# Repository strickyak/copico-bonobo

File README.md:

# copico-bonobo
KICAD: Simple and cheap PI PICO cartridge for Coco; can spoonfeed to boot, and has Control &amp; Data ports decoded.

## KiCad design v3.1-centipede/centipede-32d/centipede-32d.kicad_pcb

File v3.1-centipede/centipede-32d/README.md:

# Centipede 32d

TO DO -- document better.

This is pretty much a RP2350B microcontroller with direct connections
to the Radio Shack Color Computer's 40-pin expansion bus.

The RP2350B may be powered either by the USB-C or by the Coco.
The USB-C takes precedence by going through only one diode
to VBUS, whereas the Coco's +5V input goes through two diodes.

Jumper J6 must be configured in one of two ways:

*   Preferred: Connect pins 2 and 3, and connect pins 4 and 5.
    This runs both E and Q through the schmidt trigger inverter
    to clean them.   They arrive negated at GPIO 21 and 22.

*   Original:  Connect pins 1 and 2, and pins 5 and 6.
    This runs E and Q direct to GPIO 21 and 22, not negated.
    This has problems with bouncy detection.

## Maybe a BUG? VBUS powers the 74HC14.

## Bug: CTS

On a coco3, we must obey CTS, not just the address range $C000-$DFFF.

Temporarily I'm bodging it from J5 to J4, CTS (negative logic) to GPIO18.

## Clock Speed

My current PIO-less firmware works with the semi-fast poke ($FFD7)
but not with the fast poke ($FFD9).   That's with disk11.asm for
Disk Basic Cart ROM, and a floppy at $FF40/$FF4[89AB].

Testing on a 16K Coco2 (named "2C") and a Coco3 with a 6309
and 512K RAM (named "3B").

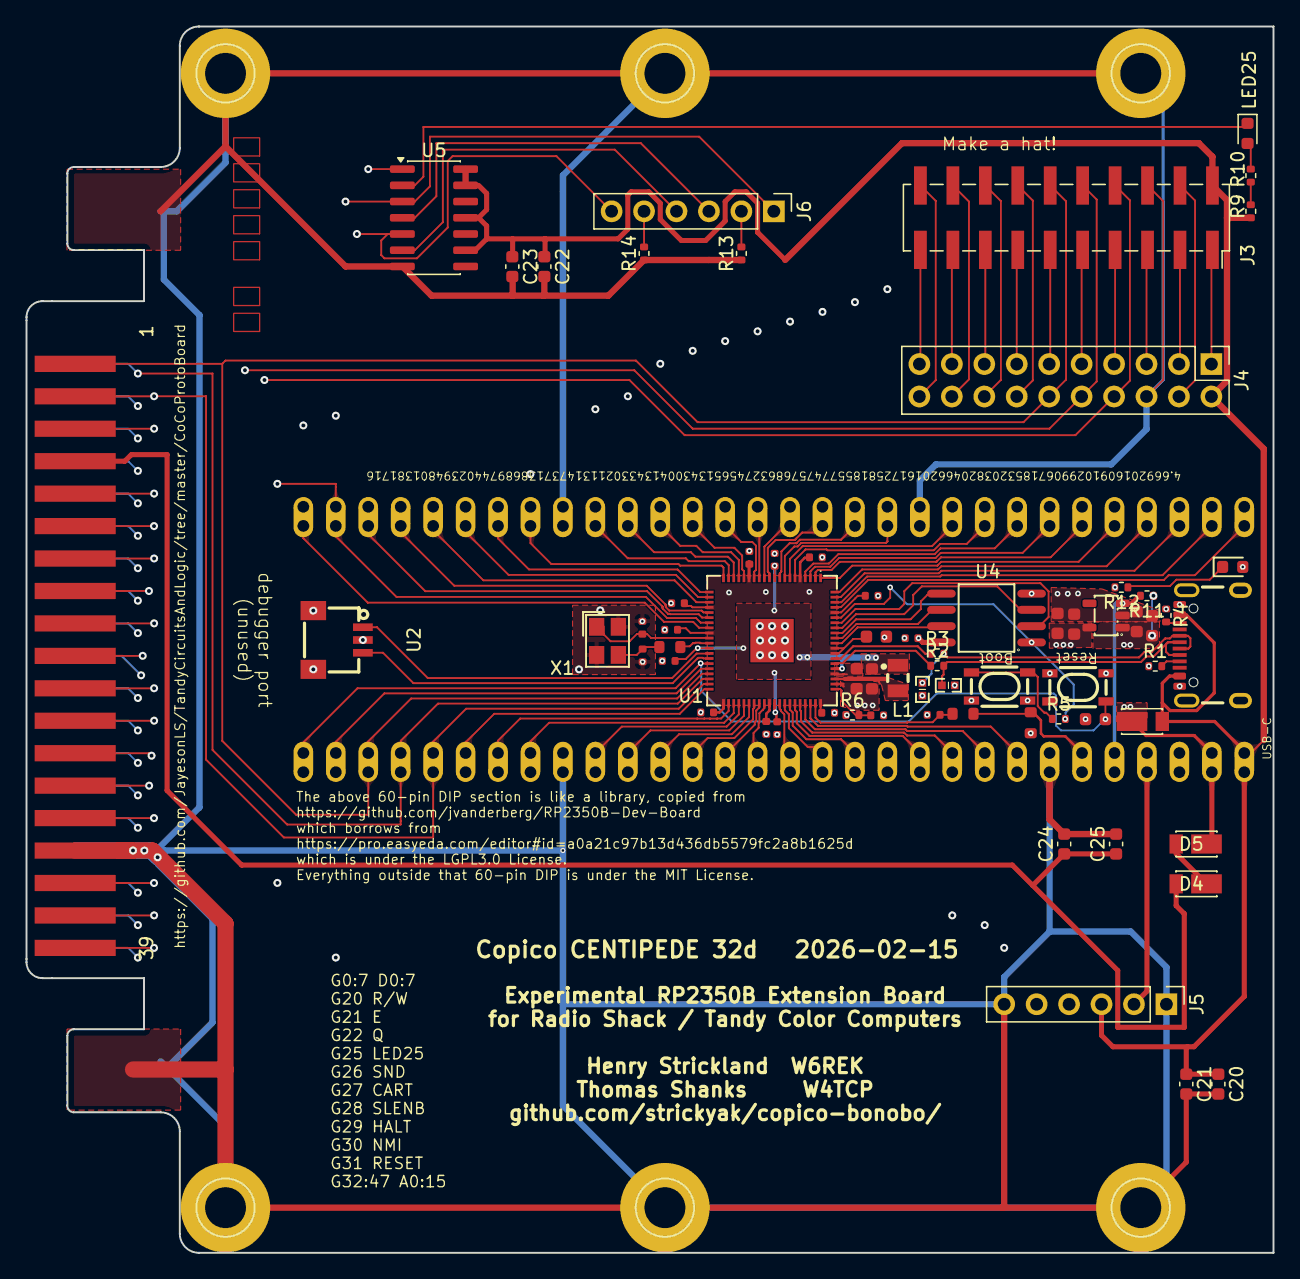
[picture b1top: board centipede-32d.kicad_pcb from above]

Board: 4 copper layers, 97.6 x 96.0 mm, 127 parts (0 on the bottom side), 89 nets.

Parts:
3V3_EN1, 3V31: Castellated Pad
ADC_VREF1: Castellated Pad
Boot1: K2-1808SN-A4SW-01; KEY-SMD_4P-L4.2-W3.2-P2.20-LS5.1-TL
C1, C2, C3, C4, C5, C6, C7, C8, C13, C14, C16, C36: 100nF; C_0402
C9, C15, C38, C39: 100nF; C_0603
C10, C12: 4.7uF; C_0603
C11, C19: 4.7uF; C_0402
C17, C18: 15pF; C_0402
C20, C22, C24: 10uF; C_0603_1608Metric
C21, C23, C25: 100nF; C_0603_1608Metric
C37, C40: 10uF; C_0603
D1, D4, D5: POWERDI-123_L2.8-W1.8-LS3.7-RD
D2, D3: RCLAMP0521P.TCT-MS; D0402-BI
GND1, GND2, GND3, GND4, GND4#2, GND6: Castellated Pad
GPI10: Castellated Pad
GPIO0, GPIO1, GPIO1#2, GPIO1#3, GPIO1#4, GPIO1#5, GPIO1#6, GPIO1#7, GPIO1#8, GPIO2, GPIO3, GPIO4, GPIO5, GPIO7, GPIO8, GPIO11, GPIO12, GPIO13, GPIO15, GPIO16, GPIO17, GPIO18, GPIO19, GPIO21, GPIO21#2, GPIO22, GPIO24, GPIO25, GPIO26, GPIO27, GPIO28, GPIO29, GPIO30, GPIO32, GPIO34, GPIO35, GPIO36, GPIO37, GPIO38, GPIO39, GPIO40, GPIO41, GPIO42, GPIO43, GPIO44, GPIO45, GPIO46: Castellated Pad
J3: Conn_02x10_Odd_Even; PinSocket_2x10_P2.54mm_Vertical_SMD
J4: Conn_02x10_Odd_Even; PinHeader_2x10_P2.54mm_Vertical
J5, J6: Conn_01x06; PinHeader_1x06_P2.54mm_Vertical
L1: IND-SMD_L2.0-W1.6_AOTA-B201610S3R3-101-T
LED25: Red; LED_0603_1608Metric
P1: CocoEdgeConnector; CocoCardEdgeCocoMIDI
PWR_LED1: Red; D_0603
R1, R4: 5.1kΩ; R_0402_1005Metric
R2, R3, R6: 33Ω; R_0402_1005Metric
R5: 1kΩ; R_0402_1005Metric
R7: 1Ω; R_0603
R8: 200Ω; R_0603
R9, R10, R12: 2kΩ; R_0402_1005Metric
R11: 100kΩ; R_0402_1005Metric
R13, R14: 10kΩ; R_0402_1005Metric
R28: 1kΩ; R_0603
RUN1: Castellated Pad
Reset1: K2-1808SN-A4SW-01; KEY-SMD_4P-L4.2-W3.2-P2.20-LS5.1-TL
U1: QFN-80_L10.0-W10.0-P0.40-TL-EP3.4
U2: HC-1.0-3PWT; CONN-SMD_SM03B-SRSS-TB-LF-SN-P
U3: SOT-23-5_L3.0-W1.7-P0.95-LS2.8-BR
U4: W25Q128; SOIC-8_L5.3-W5.3-P1.27-LS8.0-BL
U5: 74HC14; SOIC-14_3.9x8.7mm_P1.27mm
USB1: USB-C-SMD_TYPE-C-6PIN-2MD-073
VBUS1: Castellated Pad
VSYS1: Castellated Pad
X1: CRYSTAL-SMD_4P-L3.2-W2.5-BL

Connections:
1V1: C2.1, C5.1, C10.2, C13.2, L1.2, U1.10 (DVDD), U1.32 (DVDD), U1.51 (DVDD), U1.65 (VREG_FB)
3V3: 3V31.57, C1.1, C3.1, C4.1, C6.1, C7.1, C8.2, C9.2, C12.2, C14.2, C16.2, C36.2, C38.1, C40.1, J3.4, J4.4, J5.2, PWR_LED1.2, R6.1, R8.2, U1.5 (IOVDD), U1.15 (IOVDD), U1.24 (IOVDD), U1.29 (IOVDD), U1.41 (IOVDD), U1.50 (IOVDD), U1.60 (IOVDD), U1.64 (VREG_VIN), U1.68 (USB_OTP_VDD), U1.69 (QSPI_IOVDD), U1.76 (IOVDD), U3.5 (VOUT), U4.8 (VCC)
3V3_EN: 3V3_EN1.56, R11.2, U3.3 (CE)
/VREG_LX: L1.1, U1.63 (VREG_LX)
ADC_VREF: ADC_VREF1.55, R7.2, R8.1
Coco5V: C24.1, C25.1, D4.2, P1.9 (+5V)
Eclock: J6.1, P1.6 (E), U5.3
GND: Boot1.3, Boot1.4, C1.2, C2.2, C3.2, C4.2, C5.2, C6.2, C7.2, C8.1, C9.1, C10.1, C11.1, C12.1, C13.1, C14.1, C15.1, C16.1, C17.2, C18.1, C19.2, C20.2, C21.2, C22.2, C23.2, C24.2, C25.2, C36.1, C37.2, C38.2, C39.2, C40.2, D2.1, D3.1, GND2.22, GND3.39, GND4.49, GND4#2.54, GND6.58, GPI10.11, J3.6, J4.6, J5.1, J5.6, P1.33 (GND), P1.34 (GND), R1.1, R4.1, R12.2, R13.1, R14.1, Reset1.3, Reset1.4, U1.62 (VREG_PGND), U1.81 (GND), U2.2, U2.4, U2.5, U3.2 (VSS), U4.4 (GND), U5.7 (GND), USB1.1 (GND), USB1.12 (GND), USB1.13 (SHELL), USB1.14 (SHELL), X1.2 (GND), X1.4 (GND)
GPIO0: GPIO0.1, P1.10 (D0), U1.77 (GPIO0)
GPIO1: GPIO1#2.2, P1.11 (D1), U1.78 (GPIO1)
GPIO2: GPIO2.3, P1.12 (D2), U1.79 (GPIO2)
GPIO3: GPIO3.4, P1.13 (D3), U1.80 (GPIO3)
GPIO4: GPIO4.5, P1.14 (D4), U1.1 (GPIO4)
GPIO5: GPIO5.6, P1.15 (D5), U1.2 (GPIO5)
GPIO6: GPIO1#8.7, P1.16 (D6), U1.3 (GPIO6)
GPIO7: GPIO7.8, P1.17 (D7), U1.4 (GPIO7)
GPIO8: GPIO8.9, J3.1, J4.1, U1.6 (GPIO8)
GPIO9: GPIO1#7.10, J3.3, J4.3, U1.7 (GPIO9)
GPIO10: GND1.12, J3.5, J4.5, U1.8 (GPIO10)
GPIO11: GPIO11.13, J3.7, J4.7, U1.9 (GPIO11)
GPIO12: GPIO12.14, J3.9, J4.9, U1.11 (GPIO12)
GPIO13: GPIO13.15, J3.11, J4.11, U1.12 (GPIO13)
GPIO14: GPIO1#6.16, J3.13, J4.13, U1.13 (GPIO14)
GPIO15: GPIO15.17, J3.15, J4.15, U1.14 (GPIO15)
GPIO16: GPIO16.18, J3.17, J4.17, U1.16 (GPIO16)
GPIO17: GPIO17.19, J3.19, J4.19, U1.17 (GPIO17)
GPIO18: GPIO18.20, J3.20, J4.20, U1.18 (GPIO18)
GPIO19: GPIO19.21, J3.18, J4.18, U1.19 (GPIO19)
GPIO20: GPIO21.23, P1.18 (R/~W), U1.20 (GPIO20)
GPIO21: GPIO21#2.24, J6.2, R13.2, U1.21 (GPIO21)
GPIO22: GPIO22.25, J6.5, R14.2, U1.22 (GPIO22)
GPIO23: GPIO1#5.26, U1.23 (GPIO23)
GPIO24: GPIO24.27, U1.25 (GPIO24)
GPIO25: GPIO25.28, U1.26 (GPIO25), U5.1
GPIO26: GPIO26.29, J3.16, J4.16, P1.35 (SND), U1.27 (GPIO26)
GPIO27: GPIO27.30, J3.14, J4.14, P1.8 (~CART), U1.28 (GPIO27)
GPIO28: GPIO28.31, P1.40 (~SLENB), U1.36 (GPIO28)
GPIO29: GPIO29.33, J3.12, J4.12, P1.3 (~HALT), U1.37 (GPIO29)
GPIO30: GPIO30.34, J3.10, J4.10, P1.4 (~NMI), U1.38 (GPIO30)
GPIO31: GPIO1#4.1, GPIO1#4.35, J3.8, J4.8, P1.5 (~RESET), U1.39 (GPIO31)
GPIO32: GPIO1.36, P1.19 (A0), U1.40 (GPIO32)
GPIO33: GPIO32.37, P1.20 (A1), U1.42 (GPIO33)
GPIO34: GPIO34.38, P1.21 (A2), U1.43 (GPIO34)
GPIO35: GPIO35.40, P1.22 (A3), U1.44 (GPIO35)
GPIO36: GPIO36.41, P1.23 (A4), U1.45 (GPIO36)
GPIO37: GPIO37.42, P1.24 (A5), U1.46 (GPIO37)
GPIO38: GPIO38.43, P1.25 (A6), U1.47 (GPIO38)
GPIO39: GPIO39.44, P1.26 (A7), U1.48 (GPIO39)
GPIO40/ADC0: GPIO40.45, P1.27 (A8), U1.49 (GPIO40_ADC0)
GPIO41/ADC1: GPIO41.46, P1.28 (A9), U1.52 (GPIO41_ADC1)
GPIO42/ADC2: GPIO42.47, P1.29 (A10), U1.53 (GPIO42_ADC2)
GPIO43/ADC3: GPIO43.48, P1.30 (A11), U1.54 (GPIO43_ADC3)
GPIO44/ADC4: GPIO44.50, P1.31 (A12), U1.55 (GPIO44_ADC4)
GPIO45/ADC5: GPIO45.51, P1.37 (A13), U1.56 (GPIO45_ADC5)
GPIO46/ADC6: GPIO46.52, P1.38 (A14), U1.57 (GPIO46_ADC6)
GPIO47/ADC7: GPIO1#3.53, P1.39 (A15), U1.58 (GPIO47_ADC7)
LED25a: LED25.1, U5.2
LED25b: LED25.2, R10.1
unnamed: Boot1.1, Boot1.2, R5.1
unnamed: C17.1, R28.1, X1.3
unnamed: D4.1, D5.2
unnamed: PWR_LED1.1, R12.1
unnamed: R9.1, R10.2
unnamed: C19.1, R7.1, U1.59 (ADC_AVDD)
unnamed: U1.71 (QSPI_SCLK), U4.6 (CLK)
unnamed: U1.72 (QSPI_SD0), U4.5 (DI)
unnamed: U1.74 (QSPI_SD1), U4.2 (DO)
unnamed: U1.73 (QSPI_SD2), U4.3 (IO2)
unnamed: U1.70 (QSPI_SD3), U4.7 (IO3)
unnamed: R5.2, U1.75 (QSPI_SS), U4.1 (CS#)
unnamed: U1.33 (SWCLK), U2.1
unnamed: U1.34 (SWDIO), U2.3
unnamed: R2.1, U1.66 (USB_DM)
unnamed: R3.1, U1.67 (USB_DP)
unnamed: C11.2, R6.2, U1.61 (VREG_AVDD)
unnamed: C18.2, U1.30 (XIN), X1.1
unnamed: R28.2, U1.31 (XOUT)
unnamed: R1.2, USB1.4 (CC1)
unnamed: R4.2, USB1.10 (CC2)
Qclock: J6.6, P1.7 (Q), U5.5
RUN: C15.2, RUN1.30, Reset1.1, U1.35 (RUN)
USB2_D+: D3.2, R3.2, USB1.6 (DP1), USB1.8 (DP2)
USB2_D-: D2.2, R2.2, USB1.5 (DN2), USB1.7 (DN1)
VBUS: C20.1, C21.1, C22.1, C23.1, D1.2, J3.2, J4.2, J5.3, R9.2, U5.9, U5.11, U5.13, U5.14 (VCC), USB1.2 (VBUS), USB1.11 (VBUS), VBUS1.60
VSYS: C37.1, C39.1, D1.1, D5.1, R11.1, U3.1 (VIN), VSYS1.59
nCTS: J5.4, P1.32 (~CTS)
nEclock: J6.3, U5.4
nQclock: J6.4, U5.6
nSCS: J5.5, P1.36 (~SCS)

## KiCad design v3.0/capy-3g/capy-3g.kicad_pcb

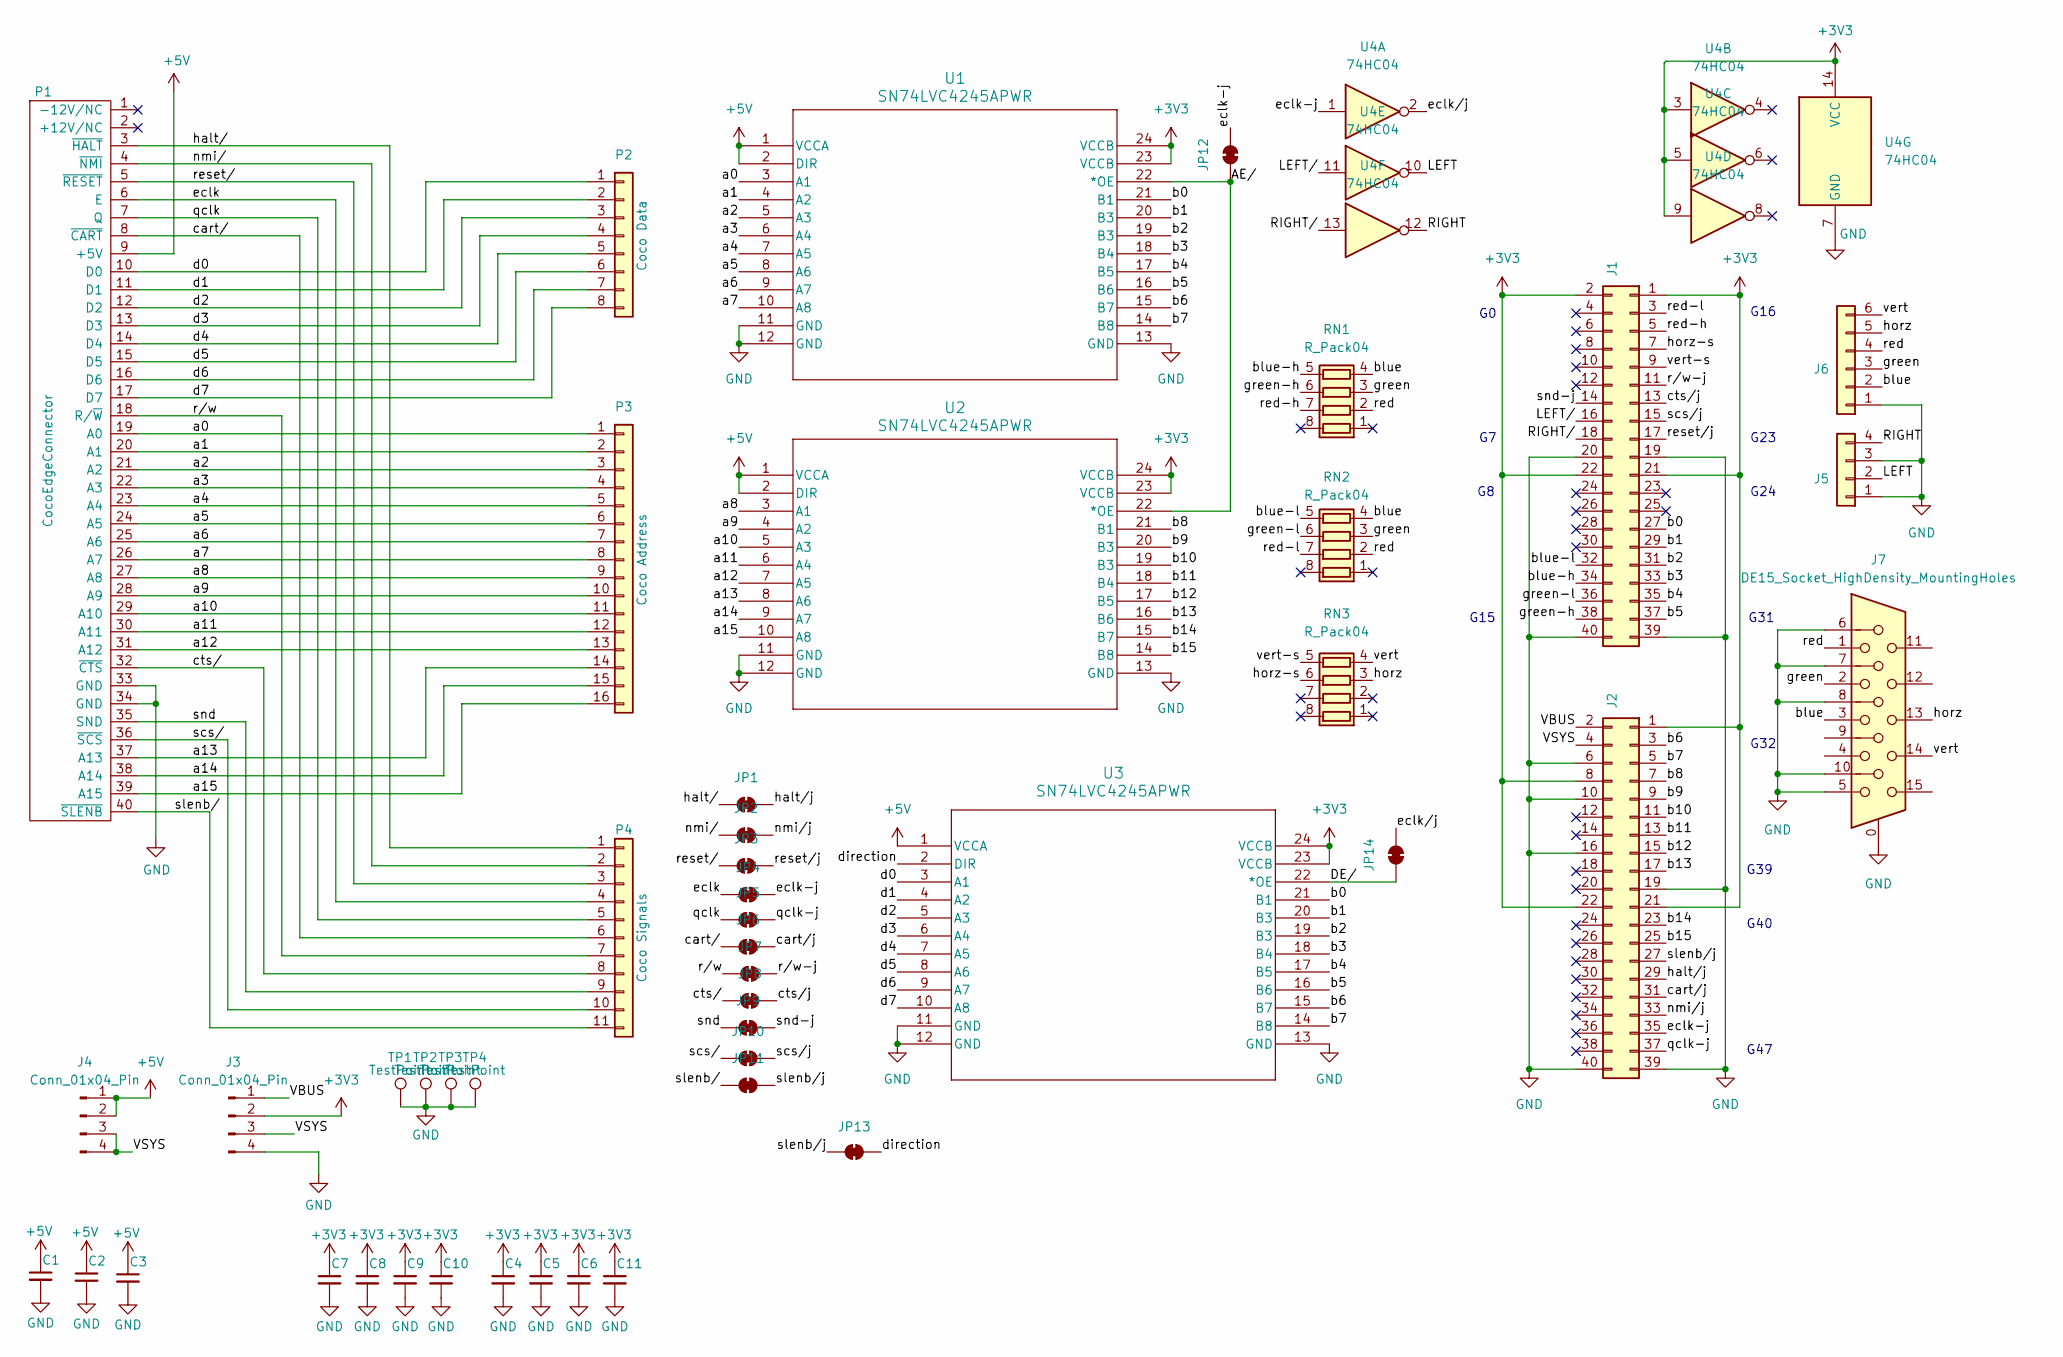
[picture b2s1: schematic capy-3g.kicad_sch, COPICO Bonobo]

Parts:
C1, C2, C3, C4, C5, C6, C7, C8, C9, C10, C11: C_Small; C_0402_1005Metric
J1, J2: Conn_02x20_Odd_Even; PinHeader_2x20_P2.54mm_Vertical
J3, J4: Conn_01x04_Pin; PinHeader_1x04_P2.54mm_Vertical
J5: Conn_01x04; PinHeader_1x04_P2.54mm_Vertical
J6: Conn_01x06; PinHeader_1x06_P2.54mm_Vertical
J7: DE15_Socket_HighDensity_MountingHoles; DSUB-15-HD_Socket_Vertical_P2.29x1.98mm_MountingHoles
JP1, JP2, JP3, JP4, JP5, JP6, JP7, JP8, JP9, JP10, JP11, JP12, JP13, JP14: SolderJumper_2_Bridged; SolderJumper-2_P1.3mm_Bridged_RoundedPad1.0x1.5mm
P1: CocoEdgeConnector; CocoCardEdgeCocoMIDI
P2: Coco Data; DIP-16_W7.62mm
P3: Coco Address; DIP-32_W15.24mm
P4: Coco Signals; DIP-22_W10.16mm
RN1, RN2, RN3: R_Pack04; R_Array_Convex_4x0603
TP1, TP2, TP3, TP4: TestPoint; TestPoint_Plated_Hole_D4.0mm
U1, U2, U3: SN74LVC4245APWR; TSSOP-24_4.4x7.8mm_P0.65mm
U4: 74HC04; TSSOP-14_4.4x5mm_P0.65mm

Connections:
+3V3: C4.1, C5.1, C6.1, C7.1, C8.1, C9.1, C10.1, C11.1, J1.1, J1.2, J1.21, J1.22, J2.1, J2.8, J2.21, J2.22, J3.2, U1.23 (VCCB), U1.24 (VCCB), U2.23 (VCCB), U2.24 (VCCB), U3.23 (VCCB), U3.24 (VCCB), U4.3, U4.5, U4.9, U4.14 (VCC)
+5V: C1.1, C2.1, C3.1, J4.1, J4.2, P1.9 (+5V), U1.1 (VCCA), U1.2 (DIR), U2.1 (VCCA), U2.2 (DIR), U3.1 (VCCA)
/AE/: JP12.1 (A), U1.22 (*OE), U2.22 (*OE)
/DE/: JP14.1 (A), U3.22 (*OE)
/LEFT: J5.2, U4.10
/LEFT/: J1.16, U4.11
/RIGHT: J5.4, U4.12
/RIGHT/: J1.18, U4.13
/VBUS: J2.2, J3.1
/VSYS: J2.4, J3.3, J4.3, J4.4
/a0: P1.19 (A0), P3.1, U1.3 (A1)
/a1: P1.20 (A1), P3.2, U1.4 (A2)
/a2: P1.21 (A2), P3.3, U1.5 (A3)
/a3: P1.22 (A3), P3.4, U1.6 (A4)
/a4: P1.23 (A4), P3.5, U1.7 (A5)
/a5: P1.24 (A5), P3.6, U1.8 (A6)
/a6: P1.25 (A6), P3.7, U1.9 (A7)
/a7: P1.26 (A7), P3.8, U1.10 (A8)
/a8: P1.27 (A8), P3.9, U2.3 (A1)
/a9: P1.28 (A9), P3.10, U2.4 (A2)
/a10: P1.29 (A10), P3.11, U2.5 (A3)
/a11: P1.30 (A11), P3.12, U2.6 (A4)
/a12: P1.31 (A12), P3.13, U2.7 (A5)
/a13: P1.37 (A13), P3.14, U2.8 (A6)
/a14: P1.38 (A14), P3.15, U2.9 (A7)
/a15: P1.39 (A15), P3.16, U2.10 (A8)
/b0: J1.27, U1.21 (B1), U3.21 (B1)
/b1: J1.29, U1.20 (B3), U3.20 (B3)
/b2: J1.31, U1.19 (B3), U3.19 (B3)
/b3: J1.33, U1.18 (B4), U3.18 (B4)
/b4: J1.35, U1.17 (B5), U3.17 (B5)
/b5: J1.37, U1.16 (B6), U3.16 (B6)
/b6: J2.3, U1.15 (B7), U3.15 (B7)
/b7: J2.5, U1.14 (B8), U3.14 (B8)
/b8: J2.7, U2.21 (B1)
/b9: J2.9, U2.20 (B3)
/b10: J2.11, U2.19 (B3)
/b11: J2.13, U2.18 (B4)
/b12: J2.15, U2.17 (B5)
/b13: J2.17, U2.16 (B6)
/b14: J2.23, U2.15 (B7)
/b15: J2.25, U2.14 (B8)
/blue: J6.2, J7.3, RN1.4 (R4.1), RN2.4 (R4.1)
/blue-h: J1.34, RN1.5 (R4.2)
/blue-l: J1.32, RN2.5 (R4.2)
/cart/: JP6.1 (A), P1.8 (~CART), P4.6
/cart/j: J2.31, JP6.2 (B)
/cts/: JP8.1 (A), P1.32 (~CTS), P4.8
/cts/j: J1.13, JP8.2 (B)
/d0: P1.10 (D0), P2.1, U3.3 (A1)
/d1: P1.11 (D1), P2.2, U3.4 (A2)
/d2: P1.12 (D2), P2.3, U3.5 (A3)
/d3: P1.13 (D3), P2.4, U3.6 (A4)
/d4: P1.14 (D4), P2.5, U3.7 (A5)
/d5: P1.15 (D5), P2.6, U3.8 (A6)
/d6: P1.16 (D6), P2.7, U3.9 (A7)
/d7: P1.17 (D7), P2.8, U3.10 (A8)
/direction: JP13.1 (A), U3.2 (DIR)
/eclk: JP4.1 (A), P1.6 (E), P4.4
/eclk-j: J2.35, JP4.2 (B), JP12.2 (B), U4.1
/eclk/j: JP14.2 (B), U4.2
/green: J6.3, J7.2, RN1.3 (R3.1), RN2.3 (R3.1)
/green-h: J1.38, RN1.6 (R3.2)
/green-l: J1.36, RN2.6 (R3.2)
/halt/: JP1.1 (A), P1.3 (~HALT), P4.1
/halt/j: J2.29, JP1.2 (B)
/horz: J6.5, J7.13, RN3.3 (R3.1)
/horz-s: J1.7, RN3.6 (R3.2)
/nmi/: JP2.1 (A), P1.4 (~NMI), P4.2
/nmi/j: J2.33, JP2.2 (B)
/qclk: JP5.1 (A), P1.7 (Q), P4.5
/qclk-j: J2.37, JP5.2 (B)
/red: J6.4, J7.1, RN1.2 (R2.1), RN2.2 (R2.1)
/red-h: J1.5, RN1.7 (R2.2)
/red-l: J1.3, RN2.7 (R2.2)
/reset/: JP3.1 (A), P1.5 (~RESET), P4.3
/reset/j: J1.17, JP3.2 (B)
/r/w: JP7.1 (A), P1.18 (R/~W), P4.7
/r/w-j: J1.11, JP7.2 (B)
/scs/: JP10.1 (A), P1.36 (~SCS), P4.10
/scs/j: J1.15, JP10.2 (B)
/slenb/: JP11.1 (A), P1.40 (~SLENB), P4.11
/slenb/j: J2.27, JP11.2 (B), JP13.2 (B)
/snd: JP9.1 (A), P1.35 (SND), P4.9
/snd-j: J1.14, JP9.2 (B)
/vert: J6.6, J7.14, RN3.4 (R4.1)
/vert-s: J1.9, RN3.5 (R4.2)
GND: C1.2, C2.2, C3.2, C4.2, C5.2, C6.2, C7.2, C8.2, C9.2, C10.2, C11.2, J1.19, J1.20, J1.39, J1.40, J2.6, J2.10, J2.16, J2.19, J2.39, J2.40, J3.4, J5.1, J5.3, J6.1, J7.0, J7.5, J7.6, J7.7, J7.8, J7.10, P1.33 (GND), P1.34 (GND), TP1.1, TP2.1, TP3.1, TP4.1, U1.11 (GND), U1.12 (GND), U1.13 (GND), U2.11 (GND), U2.12 (GND), U2.13 (GND), U3.11 (GND), U3.12 (GND), U3.13 (GND), U4.7 (GND)

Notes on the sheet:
G40
G23
G15
G31
G24
G32
G39
G47
G16

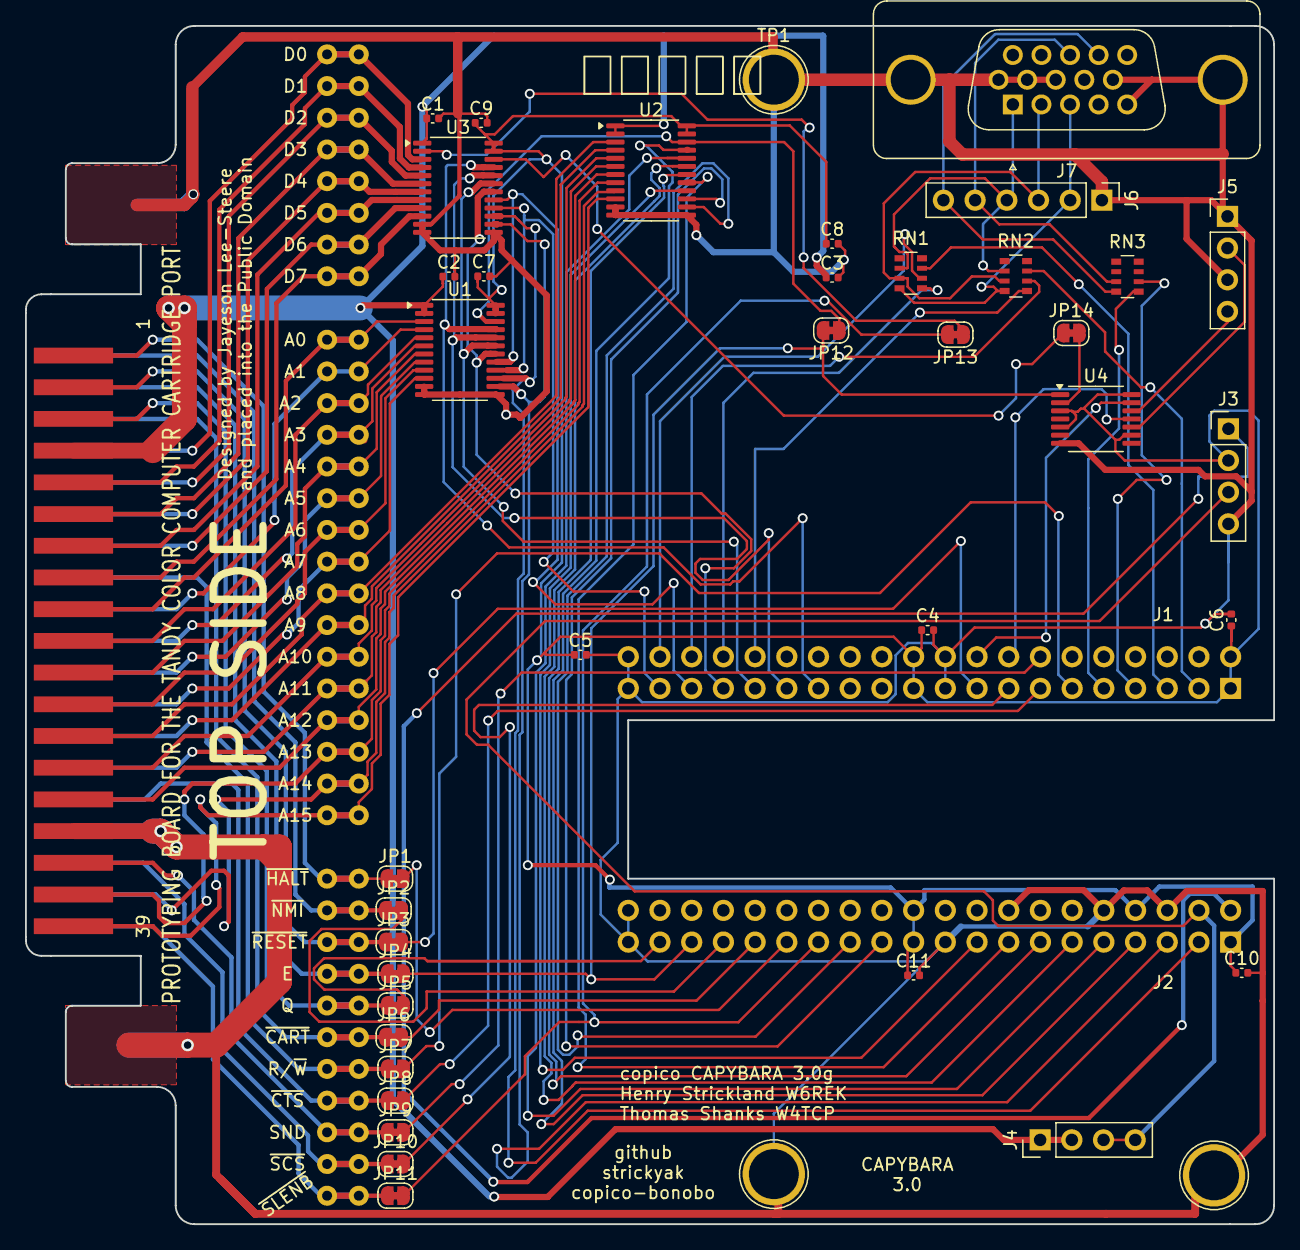
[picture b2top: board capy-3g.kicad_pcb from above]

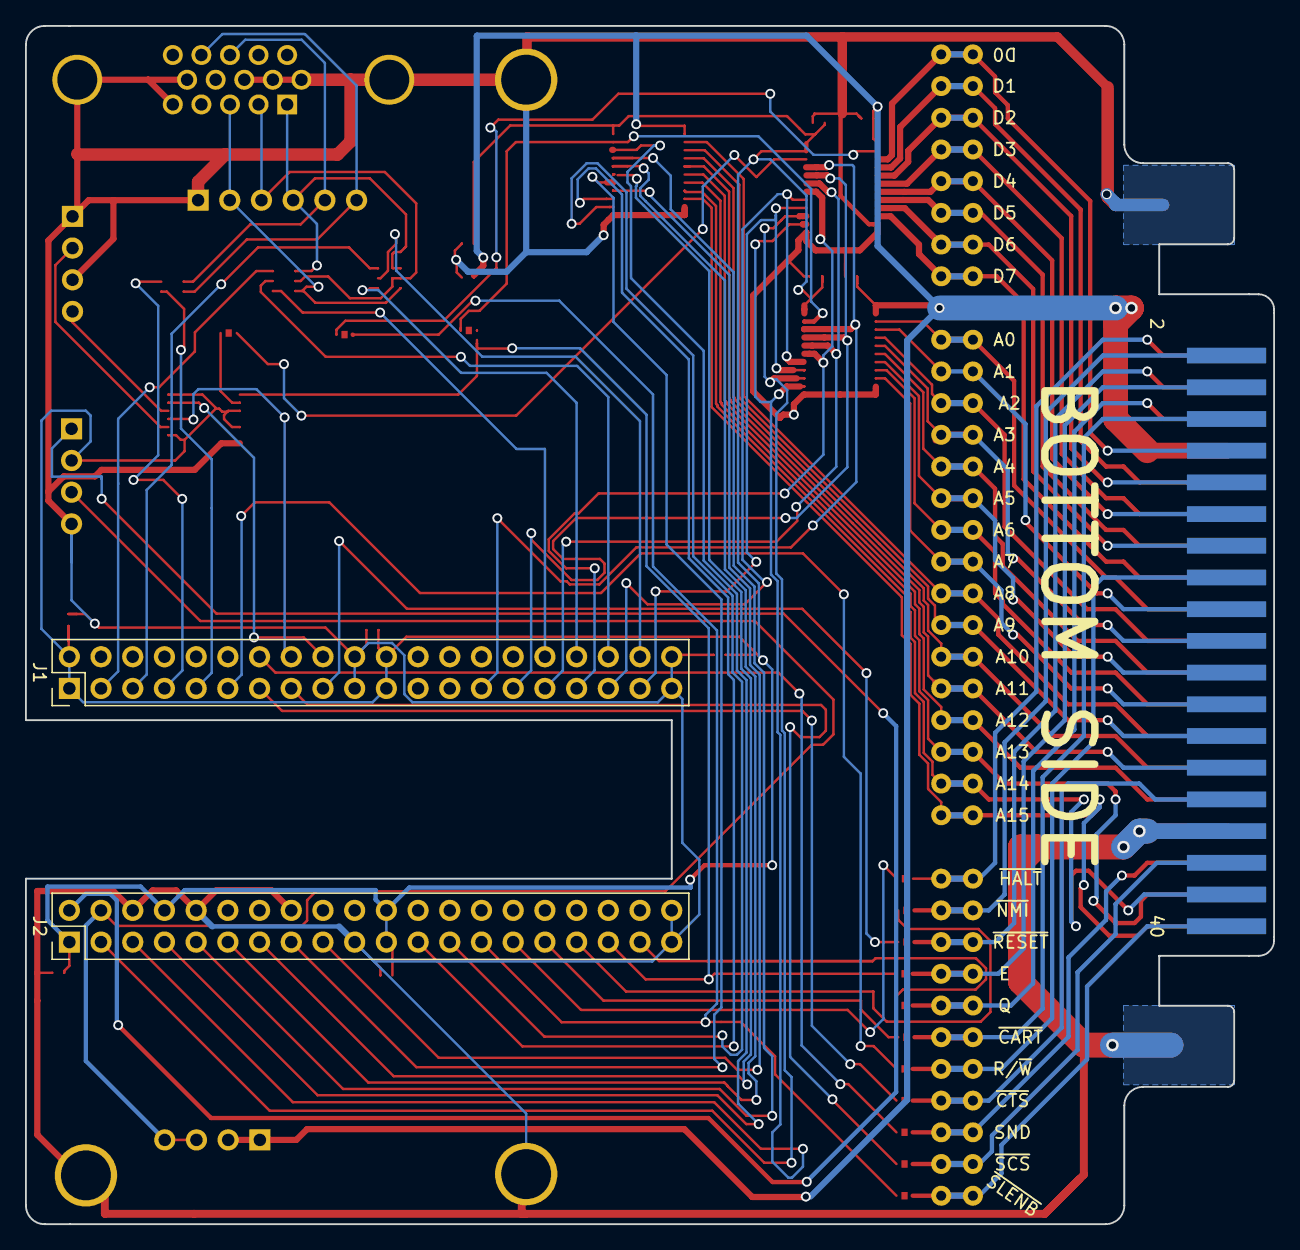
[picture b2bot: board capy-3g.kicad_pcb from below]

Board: 2 copper layers, 100.0 x 96.0 mm, 46 parts (2 on the bottom side), 88 nets.

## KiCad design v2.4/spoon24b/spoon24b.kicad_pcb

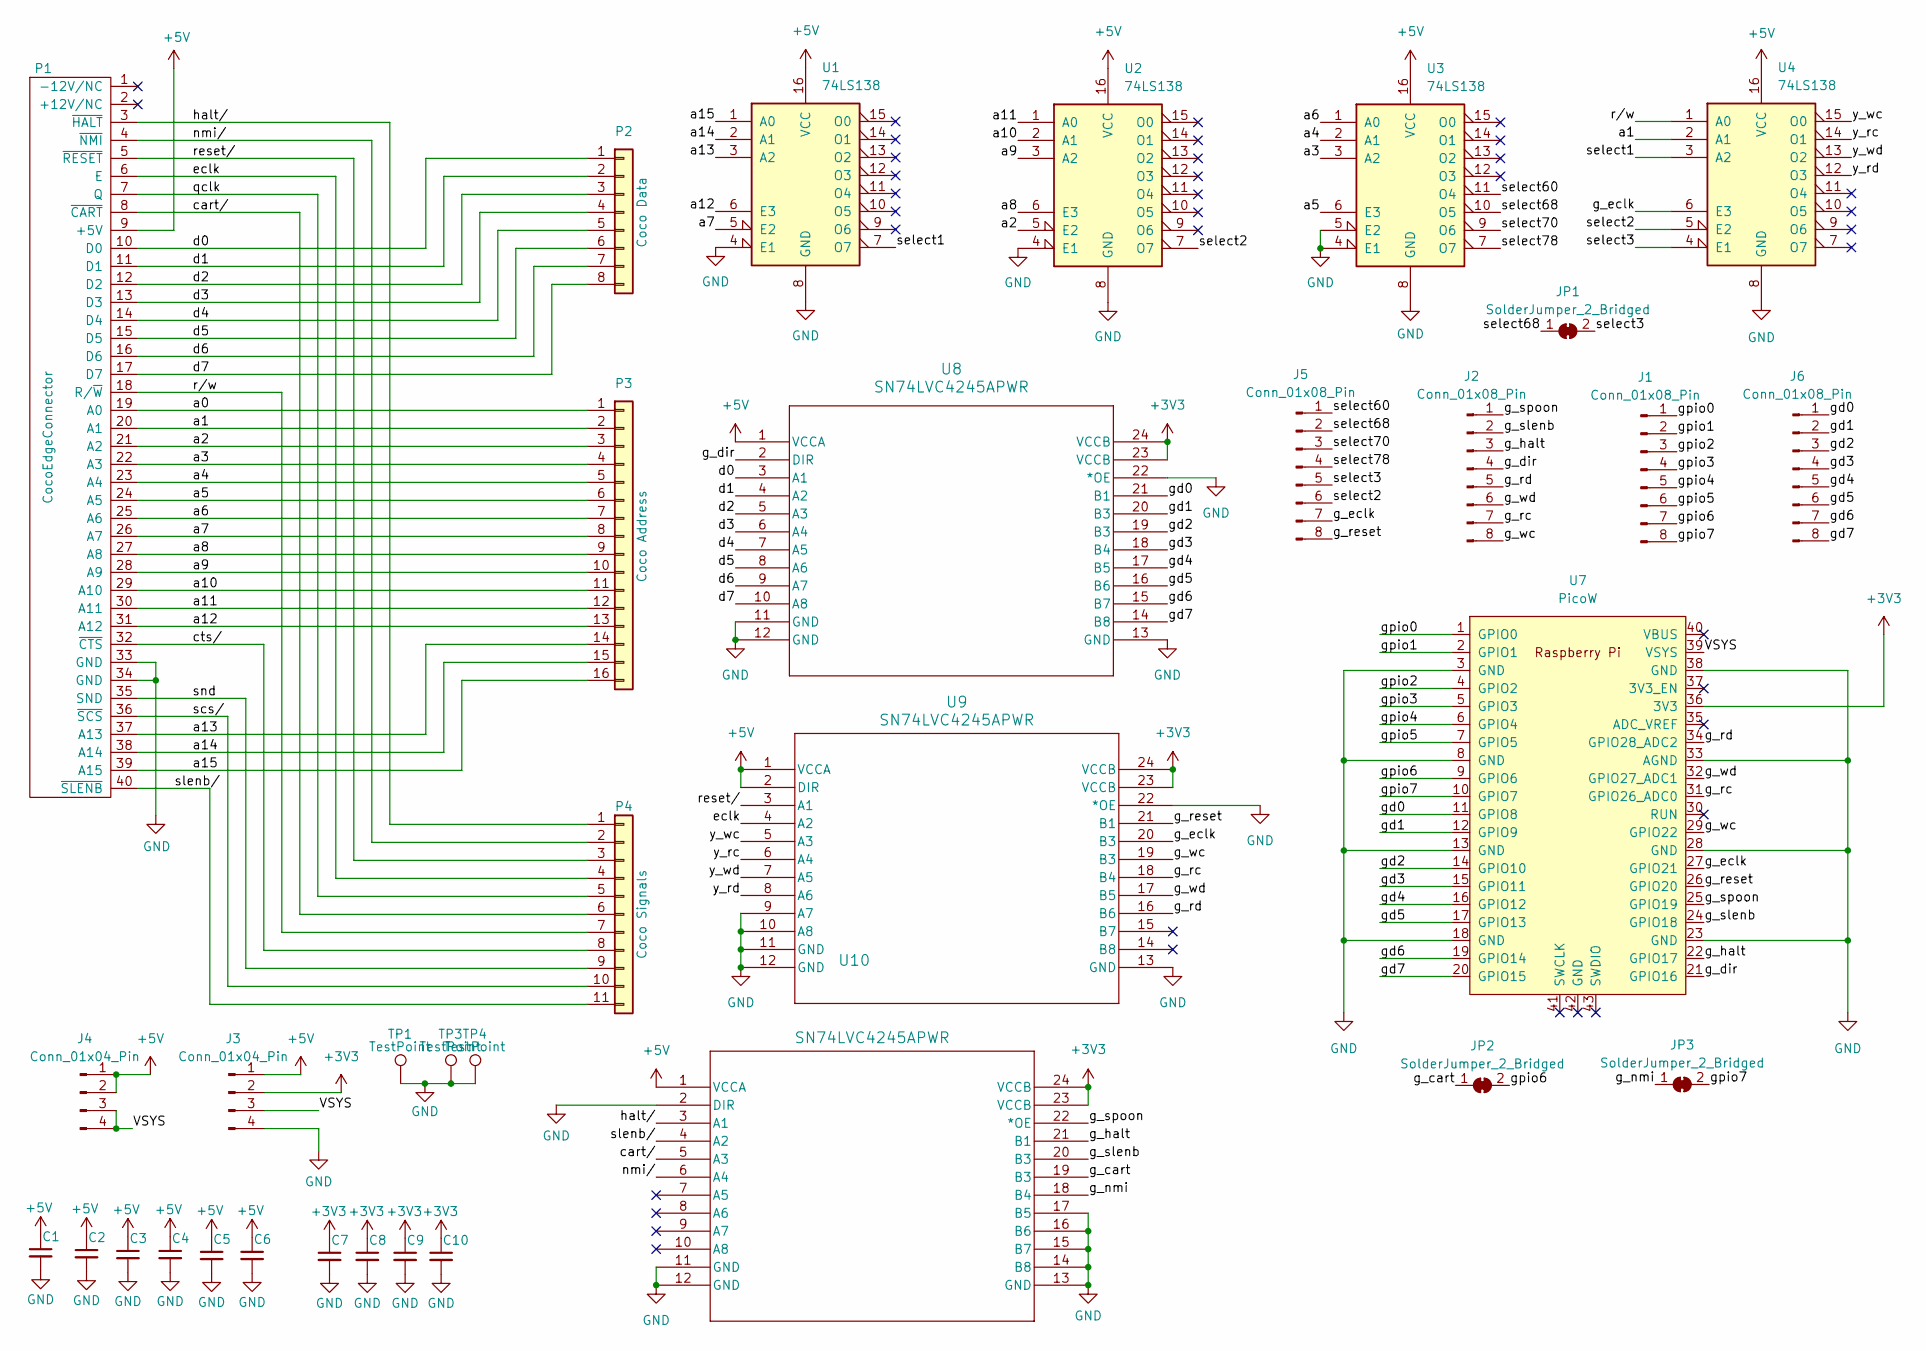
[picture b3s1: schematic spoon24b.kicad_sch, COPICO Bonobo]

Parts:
C1, C2, C3, C4, C5, C6, C7, C8, C9, C10: C_Small; C_0402_1005Metric
J1, J2, J5, J6: Conn_01x08_Pin; PinHeader_1x08_P2.54mm_Vertical
J3, J4: Conn_01x04_Pin; PinHeader_1x04_P2.54mm_Vertical
JP1, JP2, JP3: SolderJumper_2_Bridged; SolderJumper-2_P1.3mm_Bridged_Pad1.0x1.5mm
P1: CocoEdgeConnector; CocoCardEdgeCocoMIDI
P2: Coco Data; DIP-16_W7.62mm
P3: Coco Address; DIP-32_W15.24mm
P4: Coco Signals; DIP-22_W10.16mm
TP1, TP3, TP4: TestPoint; TestPoint_Plated_Hole_D4.0mm
U1, U2, U3, U4: 74LS138; SOIC-16_3.9x9.9mm_P1.27mm
U7: PicoW; RPi_PicoW_SMD_TH
U8, U9, U10: SN74LVC4245APWR; TSSOP-24_4.4x7.8mm_P0.65mm

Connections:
+3V3: C7.1, C8.1, C9.1, C10.1, J3.2, U7.36 (3V3), U8.23 (VCCB), U8.24 (VCCB), U9.23 (VCCB), U9.24 (VCCB), U10.23 (VCCB), U10.24 (VCCB)
+5V: C1.1, C2.1, C3.1, C4.1, C5.1, C6.1, J3.1, J4.1, J4.2, P1.9 (+5V), U1.16 (VCC), U2.16 (VCC), U3.16 (VCC), U4.16 (VCC), U8.1 (VCCA), U9.1 (VCCA), U9.2 (DIR), U10.1 (VCCA)
/VSYS: J3.3, J4.3, J4.4, U7.39 (VSYS)
/a0: P1.19 (A0), P3.1
/a1: P1.20 (A1), P3.2, U4.2 (A1)
/a2: P1.21 (A2), P3.3, U2.5 (E2)
/a3: P1.22 (A3), P3.4, U3.3 (A2)
/a4: P1.23 (A4), P3.5, U3.2 (A1)
/a5: P1.24 (A5), P3.6, U3.6 (E3)
/a6: P1.25 (A6), P3.7, U3.1 (A0)
/a7: P1.26 (A7), P3.8, U1.5 (E2)
/a8: P1.27 (A8), P3.9, U2.6 (E3)
/a9: P1.28 (A9), P3.10, U2.3 (A2)
/a10: P1.29 (A10), P3.11, U2.2 (A1)
/a11: P1.30 (A11), P3.12, U2.1 (A0)
/a12: P1.31 (A12), P3.13, U1.6 (E3)
/a13: P1.37 (A13), P3.14, U1.3 (A2)
/a14: P1.38 (A14), P3.15, U1.2 (A1)
/a15: P1.39 (A15), P3.16, U1.1 (A0)
/cart/: P1.8 (~CART), P4.6, U10.5 (A3)
/cts/: P1.32 (~CTS), P4.8
/d0: P1.10 (D0), P2.1, U8.3 (A1)
/d1: P1.11 (D1), P2.2, U8.4 (A2)
/d2: P1.12 (D2), P2.3, U8.5 (A3)
/d3: P1.13 (D3), P2.4, U8.6 (A4)
/d4: P1.14 (D4), P2.5, U8.7 (A5)
/d5: P1.15 (D5), P2.6, U8.8 (A6)
/d6: P1.16 (D6), P2.7, U8.9 (A7)
/d7: P1.17 (D7), P2.8, U8.10 (A8)
/eclk: P1.6 (E), P4.4, U9.4 (A2)
/g_cart: JP2.1 (A), U10.19 (B3)
/g_dir: J2.4, U7.21 (GPIO16), U8.2 (DIR)
/g_eclk: J5.7, U4.6 (E3), U7.27 (GPIO21), U9.20 (B3)
/g_halt: J2.3, U7.22 (GPIO17), U10.21 (B1)
/g_nmi: JP3.1 (A), U10.18 (B4)
/g_rc: J2.7, U7.31 (GPIO26_ADC0), U9.18 (B4)
/g_rd: J2.5, U7.34 (GPIO28_ADC2), U9.16 (B6)
/g_reset: J5.8, U7.26 (GPIO20), U9.21 (B1)
/g_slenb: J2.2, U7.24 (GPIO18), U10.20 (B3)
/g_spoon: J2.1, U7.25 (GPIO19), U10.22 (*OE)
/g_wc: J2.8, U7.29 (GPIO22), U9.19 (B3)
/g_wd: J2.6, U7.32 (GPIO27_ADC1), U9.17 (B5)
/gd0: J6.1, U7.11 (GPIO8), U8.21 (B1)
/gd1: J6.2, U7.12 (GPIO9), U8.20 (B3)
/gd2: J6.3, U7.14 (GPIO10), U8.19 (B3)
/gd3: J6.4, U7.15 (GPIO11), U8.18 (B4)
/gd4: J6.5, U7.16 (GPIO12), U8.17 (B5)
/gd5: J6.6, U7.17 (GPIO13), U8.16 (B6)
/gd6: J6.7, U7.19 (GPIO14), U8.15 (B7)
/gd7: J6.8, U7.20 (GPIO15), U8.14 (B8)
/gpio0: J1.1, U7.1 (GPIO0)
/gpio1: J1.2, U7.2 (GPIO1)
/gpio2: J1.3, U7.4 (GPIO2)
/gpio3: J1.4, U7.5 (GPIO3)
/gpio4: J1.5, U7.6 (GPIO4)
/gpio5: J1.6, U7.7 (GPIO5)
/gpio6: J1.7, JP2.2 (B), U7.9 (GPIO6)
/gpio7: J1.8, JP3.2 (B), U7.10 (GPIO7)
/halt/: P1.3 (~HALT), P4.1, U10.3 (A1)
/nmi/: P1.4 (~NMI), P4.2, U10.6 (A4)
/qclk: P1.7 (Q), P4.5
/reset/: P1.5 (~RESET), P4.3, U9.3 (A1)
/r/w: P1.18 (R/~W), P4.7, U4.1 (A0)
/scs/: P1.36 (~SCS), P4.10
/select1: U1.7 (O7), U4.3 (A2)
/select2: J5.6, U2.7 (O7), U4.5 (E2)
/select3: J5.5, JP1.2 (B), U4.4 (E1)
/select60: J5.1, U3.11 (O4)
/select68: J5.2, JP1.1 (A), U3.10 (O5)
/select70: J5.3, U3.9 (O6)
/select78: J5.4, U3.7 (O7)
/slenb/: P1.40 (~SLENB), P4.11, U10.4 (A2)
/snd: P1.35 (SND), P4.9
/y_rc: U4.14 (O1), U9.6 (A4)
/y_rd: U4.12 (O3), U9.8 (A6)
/y_wc: U4.15 (O0), U9.5 (A3)
/y_wd: U4.13 (O2), U9.7 (A5)
GND: C1.2, C2.2, C3.2, C4.2, C5.2, C6.2, C7.2, C8.2, C9.2, C10.2, J3.4, P1.33 (GND), P1.34 (GND), TP1.1, TP3.1, TP4.1, U1.4 (E1), U1.8 (GND), U2.4 (E1), U2.8 (GND), U3.4 (E1), U3.5 (E2), U3.8 (GND), U4.8 (GND), U7.3 (GND), U7.8 (GND), U7.13 (GND), U7.18 (GND), U7.23 (GND), U7.28 (GND), U7.33 (AGND), U7.38 (GND), U8.11 (GND), U8.12 (GND), U8.13 (GND), U8.22 (*OE), U9.9 (A7), U9.10 (A8), U9.11 (GND), U9.12 (GND), U9.13 (GND), U9.22 (*OE), U10.2 (DIR), U10.11 (GND), U10.12 (GND), U10.13 (GND), U10.14 (B8), U10.15 (B7), U10.16 (B6), U10.17 (B5)

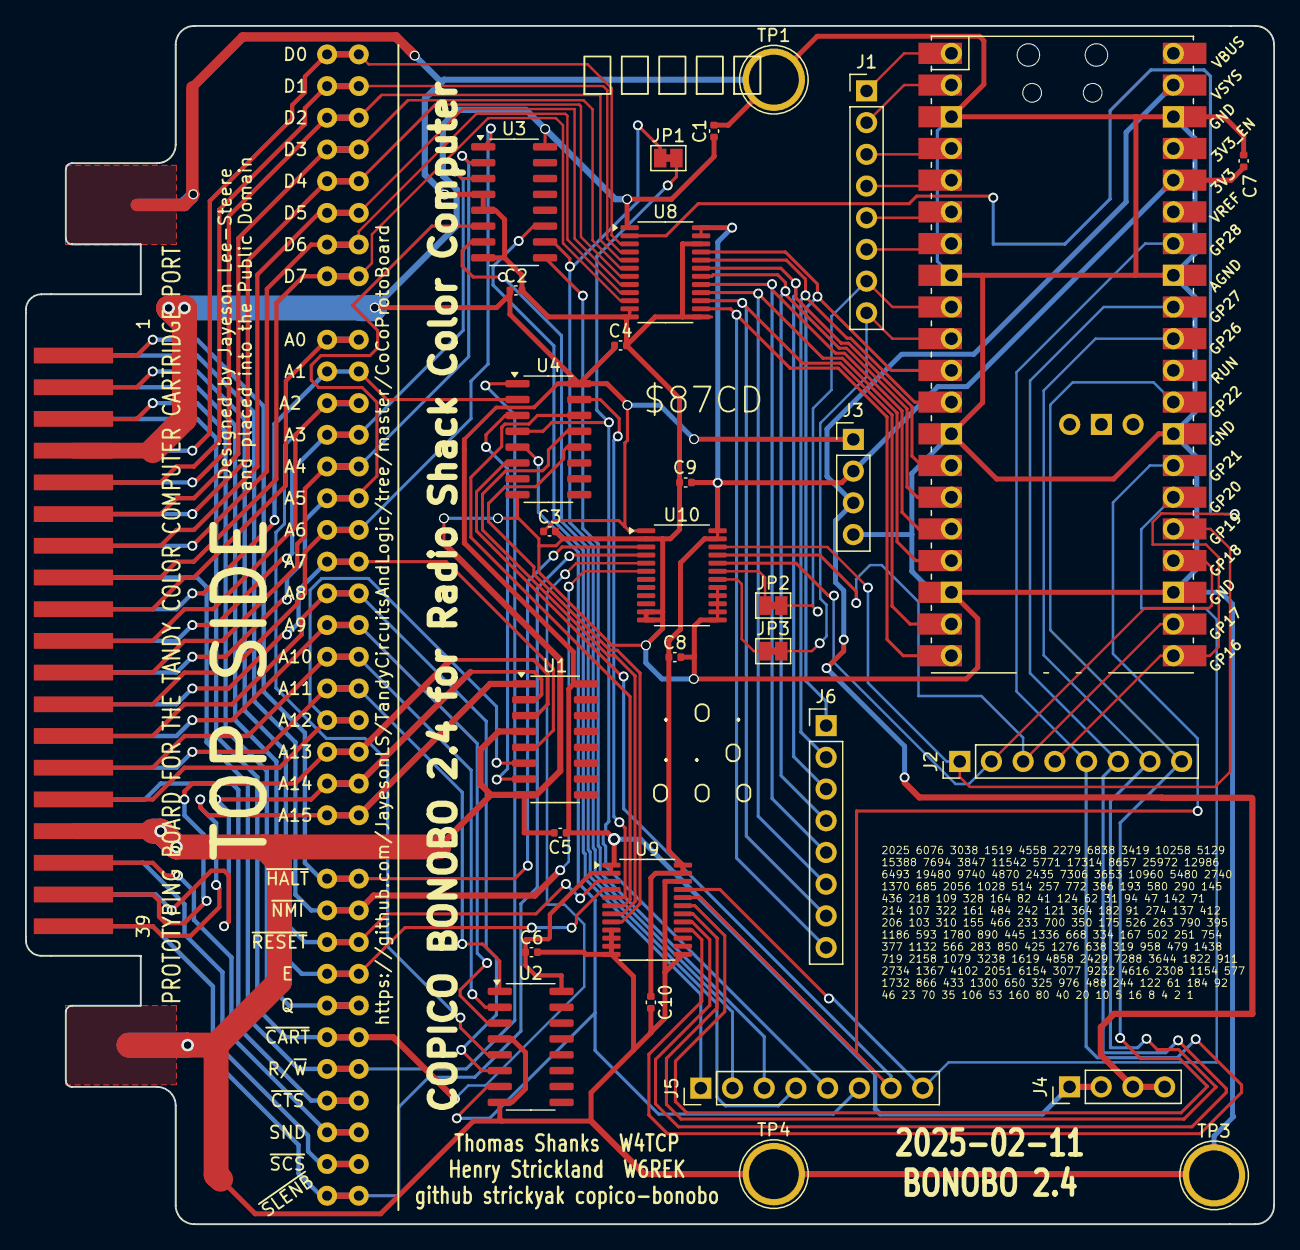
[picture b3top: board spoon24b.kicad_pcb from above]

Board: 2 copper layers, 100.0 x 96.0 mm, 34 parts (0 on the bottom side), 78 nets.

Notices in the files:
v2.4/spoon24b/spoon24b.kicad_pcb:
and placed into the Public Domain
v3.1-centipede/centipede-32d/centipede-32d.kicad_pcb:
which is under the LGPL3.0 License.
Everything outside that 60-pin DIP is under the MIT License.
